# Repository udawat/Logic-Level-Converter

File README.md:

Logic Level Converter
=====================

A Four Channel Bidirectional Logic Level Converter using NXP BSS138 MOSFETs

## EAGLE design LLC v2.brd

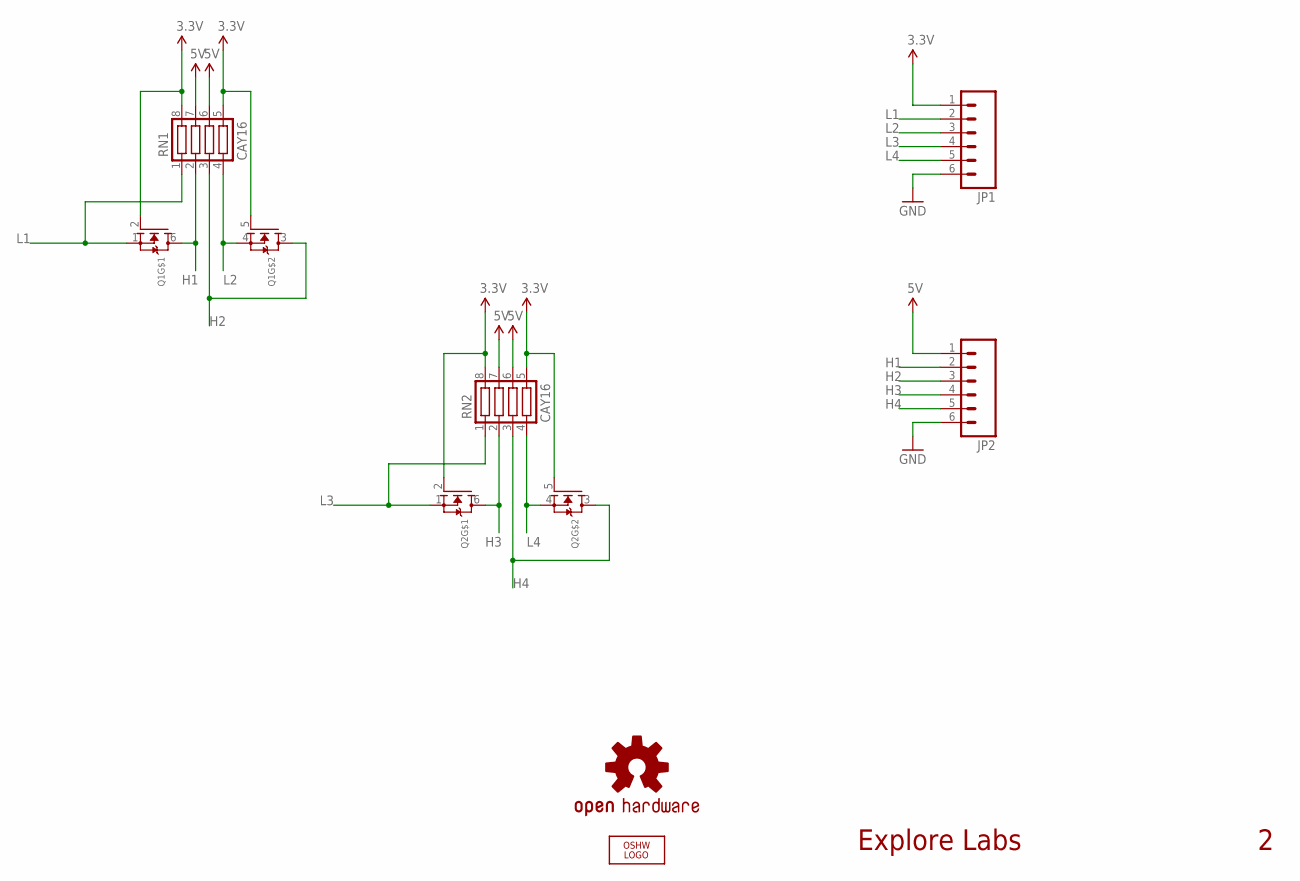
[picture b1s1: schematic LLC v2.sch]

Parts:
JP1, JP2: M06SIP; 1X06
LOGO1: OSHW_LOGO_FILLX0100-NT; OSHW_FILLX100_NOTEXT
Q1, Q2: MOSFET-N_DUAL; SOT363
RN1, RN2: CAY16; CTS742C083
U$6: OSHW-LOGOS; OSHW-LOGO-S

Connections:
3.3V: JP1.1, Q1.2 (G), Q1.5 (G), Q2.2 (G), Q2.5 (G), RN1.5, RN1.8, RN2.5, RN2.8
5V: JP2.1, RN1.6, RN1.7, RN2.6, RN2.7
GND: JP1.6, JP2.6
H1: JP2.2, Q1.6 (D), RN1.2
H2: JP2.3, Q1.3 (D), RN1.3
H3: JP2.4, Q2.6 (D), RN2.2
H4: JP2.5, Q2.3 (D), RN2.3
L1: JP1.2, Q1.1 (S), RN1.1
L2: JP1.3, Q1.4 (S), RN1.4
L3: JP1.4, Q2.1 (S), RN2.1
L4: JP1.5, Q2.4 (S), RN2.4

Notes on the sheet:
Explore Labs

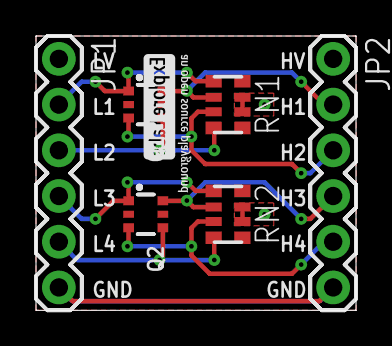
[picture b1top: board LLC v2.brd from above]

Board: 2 copper layers, 17.8 x 15.2 mm, 9 parts (1 on the bottom side), 11 nets.

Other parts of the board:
U$14: EXLABA_LOGO_0.16

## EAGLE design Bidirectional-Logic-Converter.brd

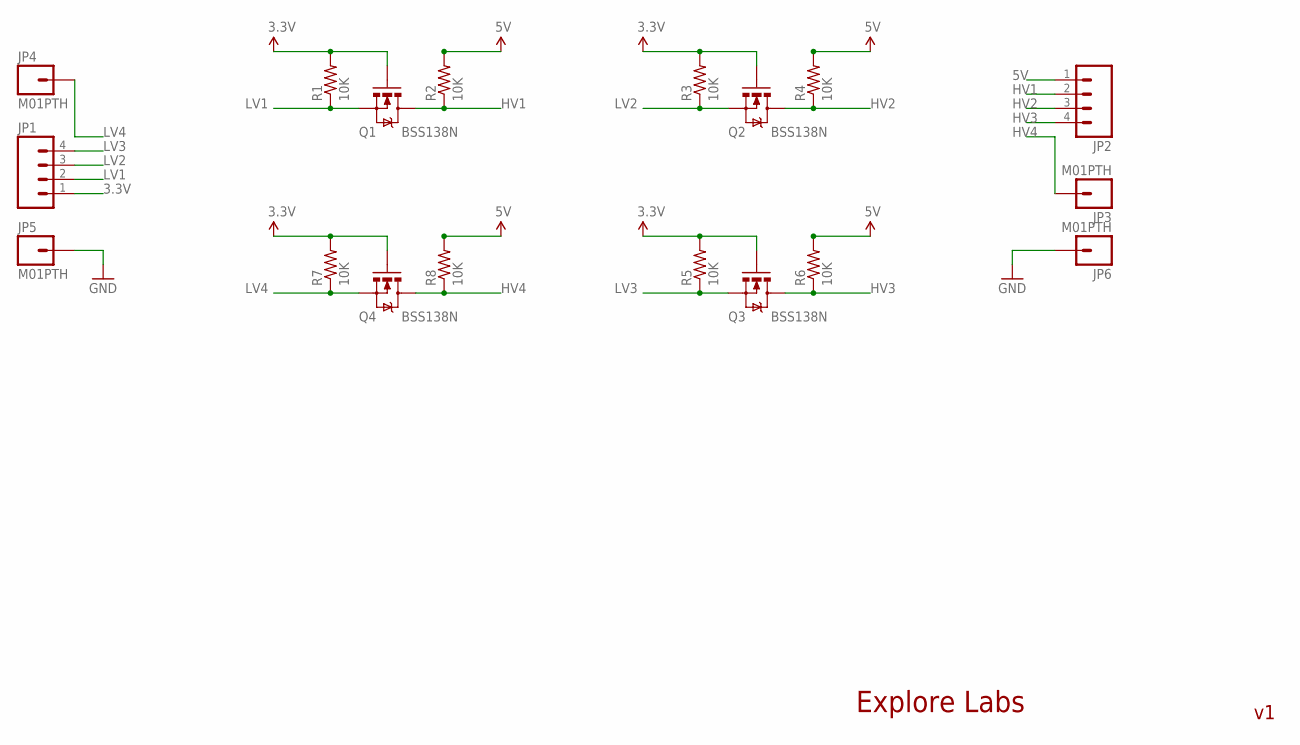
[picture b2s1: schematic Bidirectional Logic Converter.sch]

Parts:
JP1, JP2: M04PTH; 1X04
JP3, JP4, JP5, JP6: M01PTH; 1X01
Q1, Q2, Q3, Q4: BSS138N; SOT23-3
R1, R2, R3, R4, R5, R6, R7, R8: 10K; 0603-RES

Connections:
3.3V: JP1.1, Q1.1 (G), Q2.1 (G), Q3.1 (G), Q4.1 (G), R1.2, R3.2, R5.2, R7.2
5V: JP2.1, R2.2, R4.2, R6.2, R8.2
GND: JP5.1, JP6.1
HV1: JP2.2, Q1.3 (D), R2.1
HV2: JP2.3, Q2.3 (D), R4.1
HV3: JP2.4, Q3.3 (D), R6.1
HV4: JP3.1, Q4.3 (D), R8.1
LV1: JP1.2, Q1.2 (S), R1.1
LV2: JP1.3, Q2.2 (S), R3.1
LV3: JP1.4, Q3.2 (S), R5.1
LV4: JP4.1, Q4.2 (S), R7.1

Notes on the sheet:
Explore Labs

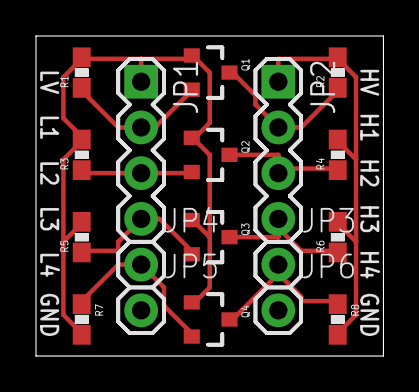
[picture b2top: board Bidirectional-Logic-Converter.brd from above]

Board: 2 copper layers, 19.3 x 17.8 mm, 18 parts (0 on the bottom side), 11 nets.

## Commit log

2012-11-22 Read me
2013-01-21 Rename...
2013-04-01 Added v2
    The newest Logic Level Converter. Still 4-channel
2013-04-06 added Gerber Data LLC v2
    updated with the latest gerber files

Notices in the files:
parts and their libraries:
SparkFun-Aesthetics: Licensing: CC v3.0 Share-Alike You are welcome to use this library for commercial purposes.
SparkFun-Aesthetics: Released under the Creative Commons
SparkFun-Aesthetics: http://creativecommons.org/licenses/by-sa/3.0
